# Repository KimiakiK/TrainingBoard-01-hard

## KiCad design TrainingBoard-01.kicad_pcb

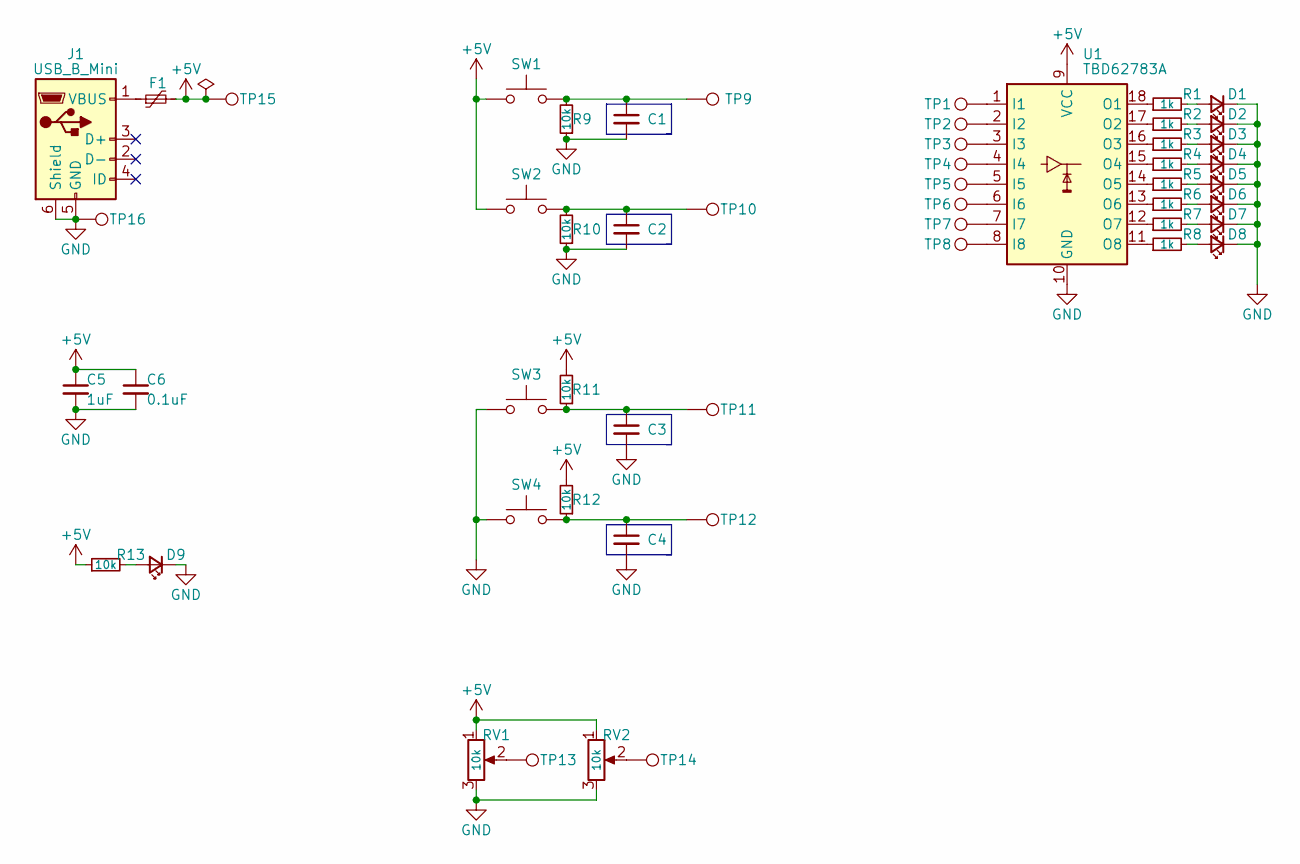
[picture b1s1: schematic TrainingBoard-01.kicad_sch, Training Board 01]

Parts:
C1, C2, C3, C4: XuF; 1608Metric
C5: 1uF; 1608Metric
C6: 0.1uF; 1608Metric
D1, D2, D3, D4, D5, D6, D7, D8, D9: LED; 1608Metric_Diode
F1: Polyfuse; 1608Metric
J1: USB_B_Mini; UX60SC-MB-5ST
R1, R2, R3, R4, R5, R6, R7, R8: 1k; 1608Metric
R9, R10, R11, R12, R13: 10k; 1608Metric
RV1, RV2: 10k; RV
SW1, SW2, SW3, SW4: SW_Push; SW_PUSH_6mm
TP1, TP2, TP3, TP4, TP5, TP6, TP7, TP8, TP9, TP10, TP11, TP12, TP13, TP14: TestPoint; TestPad_Dual
TP15, TP16: TestPoint; TestPad
U1: TBD62783A; SOP-18_7x12.5mm_P1.27mm

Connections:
+5V: C5.1, C6.1, F1.2, R11.2, R12.2, R13.1, RV1.1, RV2.1, SW1.1, SW2.1, TP15.1, U1.9 (VCC)
GND: C1.2, C2.2, C3.2, C4.2, C5.2, C6.2, D1.1 (K), D2.1 (K), D3.1 (K), D4.1 (K), D5.1 (K), D6.1 (K), D7.1 (K), D8.1 (K), D9.1 (K), J1.5 (GND), J1.6 (Shield), R9.1, R10.1, RV1.3, RV2.3, SW3.1, SW4.1, TP16.1, U1.10 (GND)
unnamed: C1.1, R9.2, SW1.2, TP9.1
unnamed: C2.1, R10.2, SW2.2, TP10.1
unnamed: C3.1, R11.1, SW3.2, TP11.1
unnamed: C4.1, R12.1, SW4.2, TP12.1
unnamed: D1.2 (A), R1.2
unnamed: D2.2 (A), R2.2
unnamed: D3.2 (A), R3.2
unnamed: D4.2 (A), R4.2
unnamed: D5.2 (A), R5.2
unnamed: D6.2 (A), R6.2
unnamed: D7.2 (A), R7.2
unnamed: D8.2 (A), R8.2
unnamed: D9.2 (A), R13.2
unnamed: F1.1, J1.1 (VBUS)
unnamed: R1.1, U1.18 (O1)
unnamed: R2.1, U1.17 (O2)
unnamed: R3.1, U1.16 (O3)
unnamed: R4.1, U1.15 (O4)
unnamed: R5.1, U1.14 (O5)
unnamed: R6.1, U1.13 (O6)
unnamed: R7.1, U1.12 (O7)
unnamed: R8.1, U1.11 (O8)
unnamed: RV1.2, TP13.1
unnamed: RV2.2, TP14.1
unnamed: TP1.1, U1.1 (I1)
unnamed: TP2.1, U1.2 (I2)
unnamed: TP3.1, U1.3 (I3)
unnamed: TP4.1, U1.4 (I4)
unnamed: TP5.1, U1.5 (I5)
unnamed: TP6.1, U1.6 (I6)
unnamed: TP7.1, U1.7 (I7)
unnamed: TP8.1, U1.8 (I8)

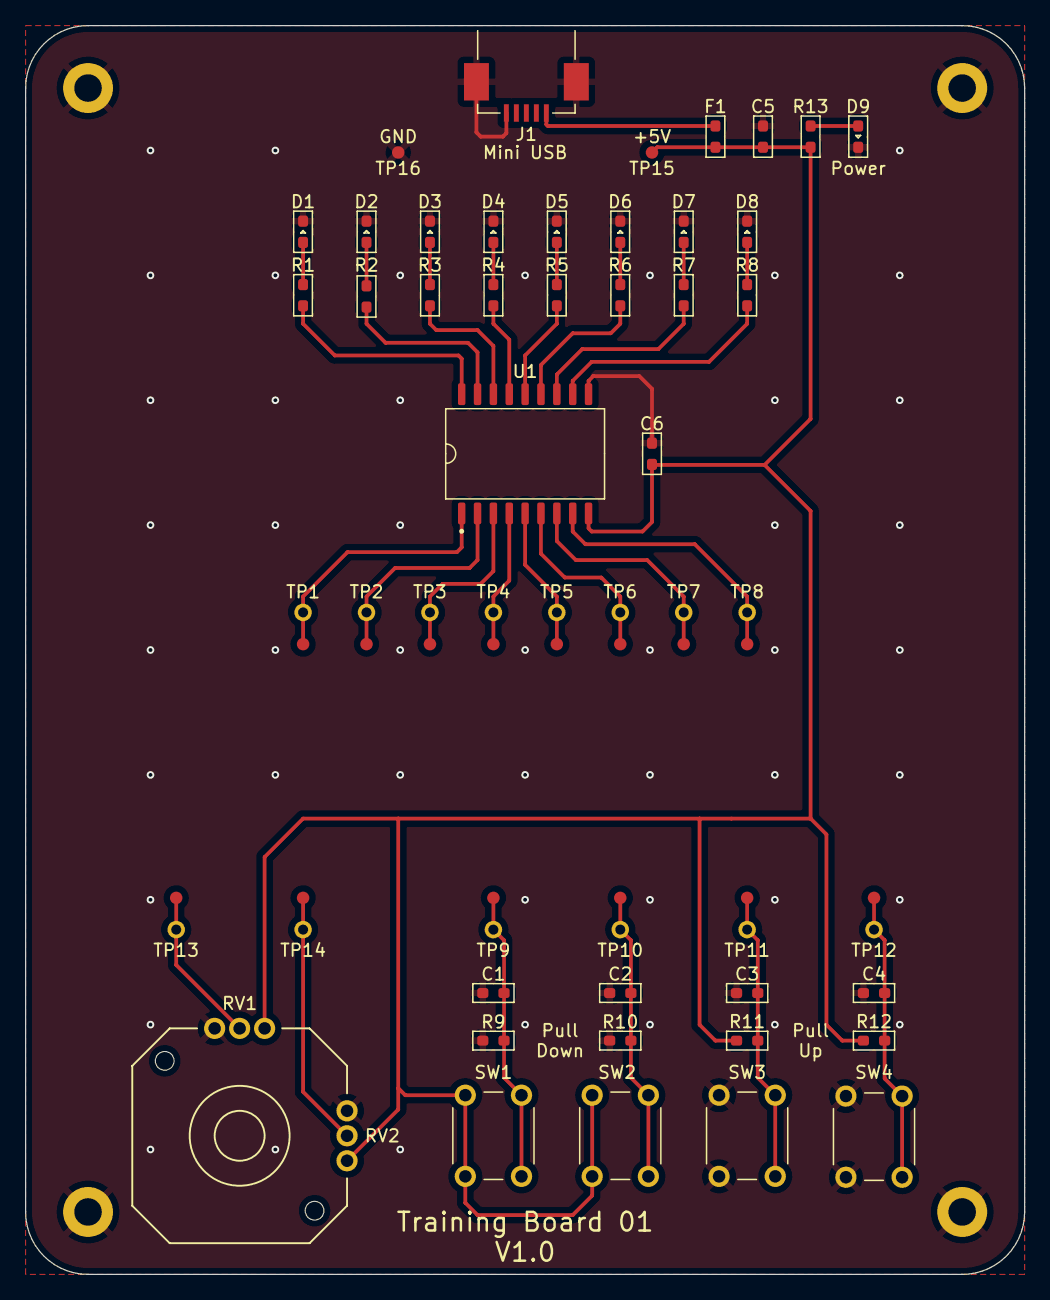
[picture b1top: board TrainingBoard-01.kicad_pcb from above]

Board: 2 copper layers, 80.0 x 100.0 mm, 53 parts (0 on the bottom side), 34 nets.

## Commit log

2022-04-01 基板 V1.0
